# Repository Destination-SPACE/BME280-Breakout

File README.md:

# BME280-Breakout
This breakout board is for the Bosch BME280 digital humidity, pressure, and temperature sensor. This board has a default I2C address of 0x77 and is **3.3V only**.

Requires symbols and footprints from [DS Global Library](https://github.com/Destination-SPACE/DS-KiCad-Global-Source)

# License
Licensed under the CERN OHLv2 - [Permissive](https://github.com/Destination-SPACE/BME280-Breakout-v2/blob/main/LICENSE) or as referenced.

(c) Destination SPACE Inc. 2022

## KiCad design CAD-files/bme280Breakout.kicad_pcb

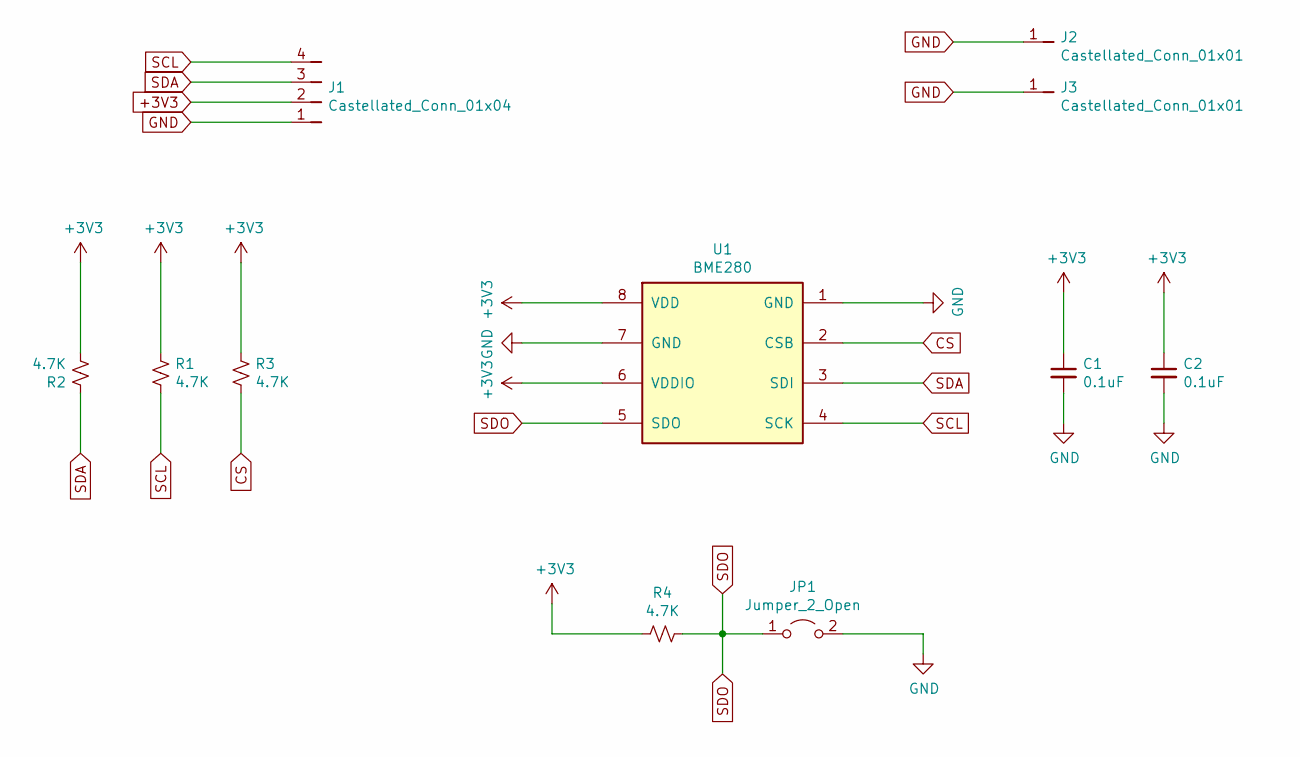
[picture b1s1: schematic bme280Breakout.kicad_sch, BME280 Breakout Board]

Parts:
C1, C2: 0.1uF; C_0805_2012Metric
J1: Castellated_Conn_01x04; Castellated_PinHeader_01x04_P2.54mm_Vertical
J2, J3: Castellated_Conn_01x01; Castellated_PinHeader_01x01_P2.54mm_Vertical
JP1: Jumper_2_Open; SolderJumper-2_P1.3mm_Open_TrianglePad1.0x1.5mm
R1, R2, R3, R4: 4.7K; R_0805_2012Metric
U1: BME280; Bosch_LGA-8_2.5x2.5mm_P0.65mm_ClockwisePinNumbering

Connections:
+3V3: C1.1, C2.1, J1.2, R1.1, R2.2, R3.1, R4.2, U1.6 (VDDIO), U1.8 (VDD)
CS: R3.2, U1.2 (CSB)
GND: C1.2, C2.2, J1.1, J2.1, J3.1, JP1.2 (B), U1.1 (GND), U1.7 (GND)
SCL: J1.4, R1.2, U1.4 (SCK)
SDA: J1.3, R2.1, U1.3 (SDI)
SDO: JP1.1 (A), R4.1, U1.5 (SDO)

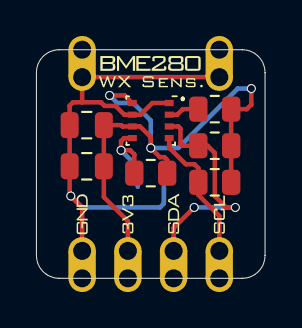
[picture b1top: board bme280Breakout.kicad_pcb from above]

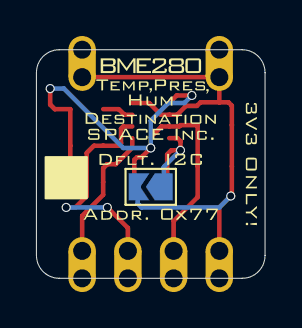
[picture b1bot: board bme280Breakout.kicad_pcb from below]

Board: 2 copper layers, 12.7 x 12.7 mm, 46 parts (18 on the bottom side), 6 nets.

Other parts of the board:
kibuzzard-62094A0D: G***; kibuzzard-62094A0D
kibuzzard-62094A2C: G***; kibuzzard-62094A2C
kibuzzard-62094A25: G***; kibuzzard-62094A25
kibuzzard-62094C8E: G***; kibuzzard-62094C8E
kibuzzard-62094C34: G***; kibuzzard-62094C34
kibuzzard-62094D35: G***; kibuzzard-62094D35
kibuzzard-62094D47: G***; kibuzzard-62094D47
kibuzzard-62094DBA: G***; kibuzzard-62094DBA
kibuzzard-62094DDC: G***; kibuzzard-62094DDC
kibuzzard-62094E12: G***; kibuzzard-62094E12
kibuzzard-62094E24, kibuzzard-62094E24#2: G***; kibuzzard-62094E24
kibuzzard-620949A9: G***; kibuzzard-620949A9
kibuzzard-620949BC: G***; kibuzzard-620949BC
kibuzzard-620949C8, kibuzzard-620949C8#2: G***; kibuzzard-620949C8
kibuzzard-620949D5, kibuzzard-620949D5#2: G***; kibuzzard-620949D5
kibuzzard-620949E0: G***; kibuzzard-620949E0
kibuzzard-620949FF, kibuzzard-620949FF#2: G***; kibuzzard-620949FF
kibuzzard-6209486A, kibuzzard-6209486A#2: G***; kibuzzard-6209486A
kibuzzard-62094851, kibuzzard-62094851#2: G***; kibuzzard-62094851
kibuzzard-62094872, kibuzzard-62094872#2: G***; kibuzzard-62094872
kibuzzard-62094878, kibuzzard-62094878#2: G***; kibuzzard-62094878
kibuzzard-62094881, kibuzzard-62094881#2: G***; kibuzzard-62094881
kibuzzard-62094889, kibuzzard-62094889#2: G***; kibuzzard-62094889
kibuzzard-62094948: G***; kibuzzard-62094948
kibuzzard-62095084: G***; kibuzzard-62095084

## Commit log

2021-09-14 Added KiCad files
2021-09-14 Create LICENSE
2021-09-28 added castellated holes

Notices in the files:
CAD-files/bme280Breakout.kicad_pcb:
Licensed under CERN OHLv2 - Permissive
